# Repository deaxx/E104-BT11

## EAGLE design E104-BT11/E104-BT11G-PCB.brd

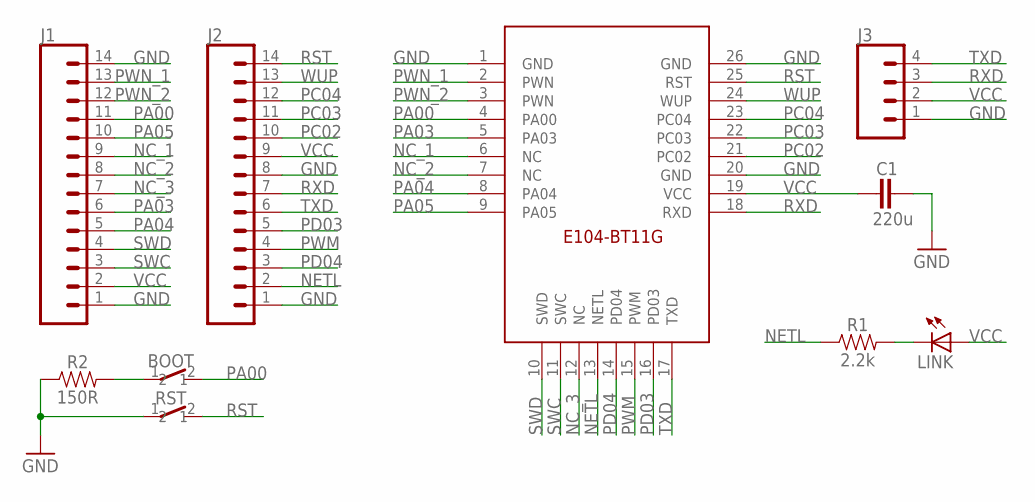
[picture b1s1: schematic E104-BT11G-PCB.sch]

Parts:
BOOT: SKRKAEE010; SKRK
C1: 220u; CAPM3528X210
J1, J2: CONN_14NO_SILK; 1X14_NO_SILK
J3: CONN_041X04_NO_SILK; 1X04_NO_SILK
LINK: LEDCHIP-LED0603; CHIP-LED0603
R1: 2.2k; 0603
R2: 150R; 0603
RST: SKRKAEE010; SKRK
U$1: E104-BT11G-PCBPCB; E104-BT11G-PCB

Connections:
GND: C1.2, J1.1, J1.14, J2.1, J2.8, J3.1, R2.1, RST.1, U$1.1 (GND), U$1.20 (GND), U$1.26 (GND)
unnamed: LINK.C, R1.2
unnamed: BOOT.1, R2.2
NC_1: J1.9, U$1.6 (NC)
NC_2: J1.8, U$1.7 (NC)
NC_3: J1.7, U$1.12 (NC)
NETL: J2.2, R1.1, U$1.13 (NETL)
PA00: BOOT.2, J1.11, U$1.4 (PA00)
PA03: J1.6, U$1.5 (PA03)
PA04: J1.5, U$1.8 (PA04)
PA05: J1.10, U$1.9 (PA05)
PC02: J2.10, U$1.21 (PC02)
PC03: J2.11, U$1.22 (PC03)
PC04: J2.12, U$1.23 (PC04)
PD03: J2.5, U$1.16 (PD03)
PD04: J2.3, U$1.14 (PD04)
PWM: J2.4, U$1.15 (PWM)
PWN_1: J1.13, U$1.2 (PWN)
PWN_2: J1.12, U$1.3 (PWN)
RST: J2.14, RST.2, U$1.25 (RST)
RXD: J2.7, J3.3, U$1.18 (RXD)
SWC: J1.3, U$1.11 (SWC)
SWD: J1.4, U$1.10 (SWD)
TXD: J2.6, J3.4, U$1.17 (TXD)
VCC: C1.1, J1.2, J2.9, J3.2, LINK.A, U$1.19 (VCC)
WUP: J2.13, U$1.24 (WUP)

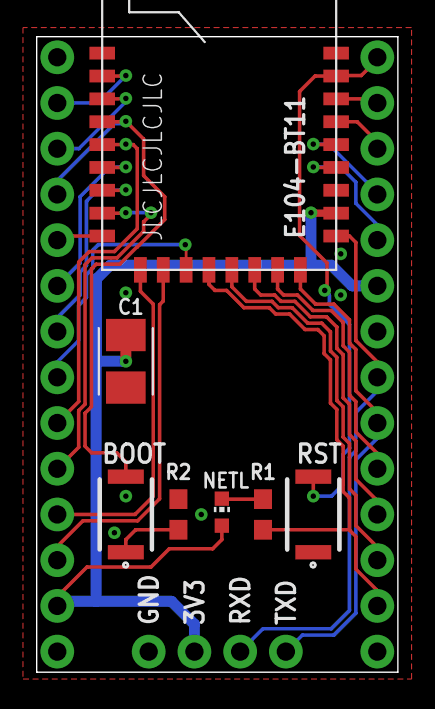
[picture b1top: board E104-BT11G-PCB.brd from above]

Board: 2 copper layers, 20.1 x 35.3 mm, 10 parts (0 on the bottom side), 26 nets.

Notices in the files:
parts and their libraries:
SparkFun-Connectors: Licensing: Creative Commons ShareAlike 4.0 International - https://creativecommons.org/licenses/by-sa/4.0
